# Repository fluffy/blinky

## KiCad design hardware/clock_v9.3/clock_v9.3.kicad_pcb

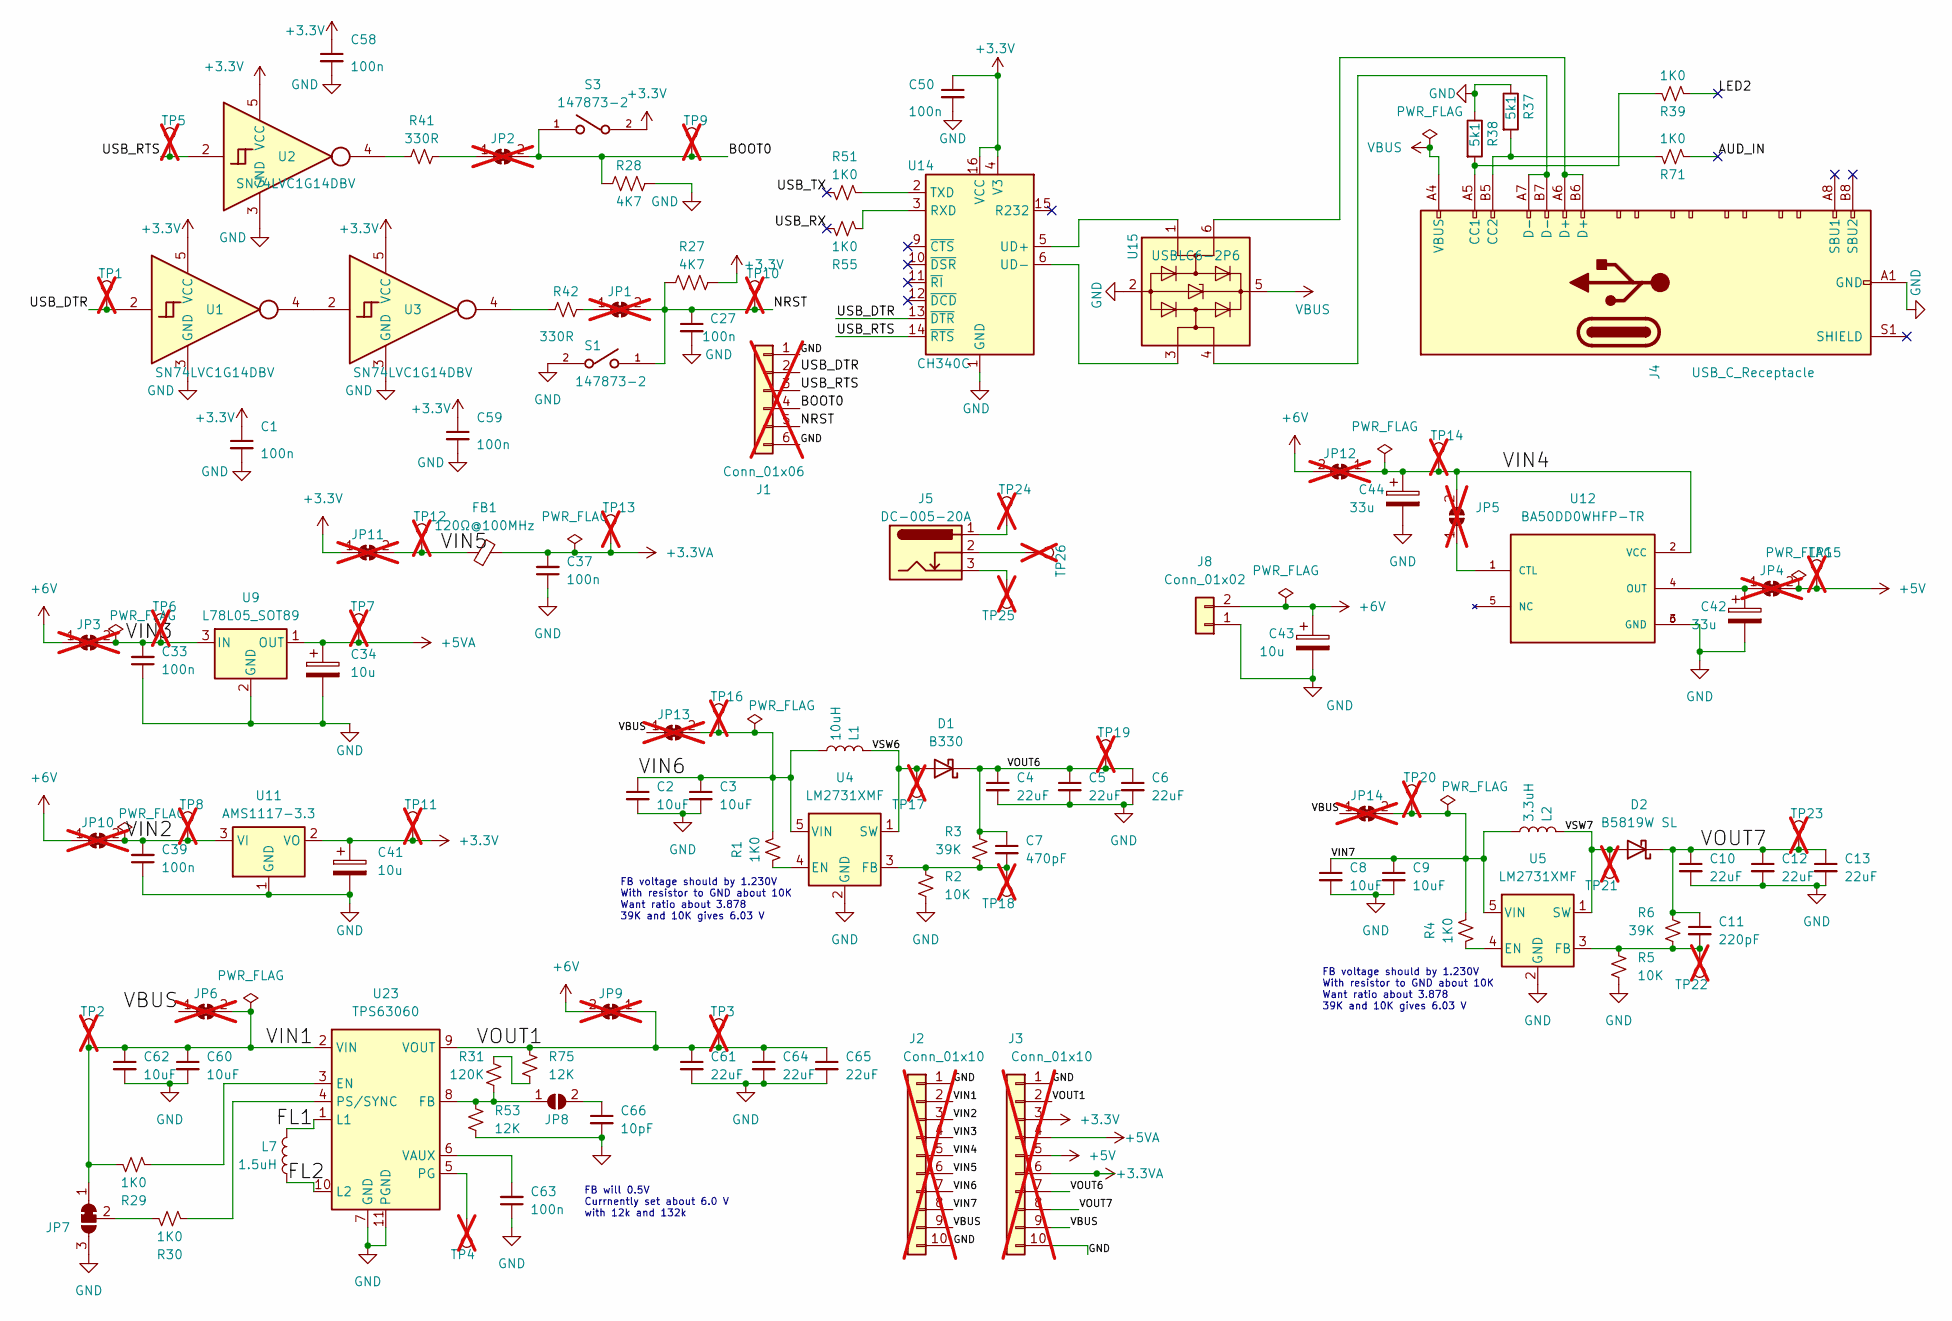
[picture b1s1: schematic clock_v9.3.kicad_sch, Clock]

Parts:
C1, C33, C39, C50, C58, C59: 100n; C_0402_1005Metric; JLCPCB Part # C307331
C2, C3, C8, C9, C60, C62: 10uF; C_0603_1608Metric; JLCPCB Part # C96446
C4, C5, C6, C10, C12, C13, C61, C64, C65: 22uF; C_0805_2012Metric; JLCPCB Part # C45783
C7: 470pF; C_0603_1608Metric; JLCPCB Part # C1620
C11: 220pF; C_0603_1608Metric; JLCPCB Part # C1603
C27, C37, C63: 100n; C_0603_1608Metric; JLCPCB Part # C14663
C34, C41, C43: 10u; CP_EIA-3216-18_Kemet-A; JLCPCB Part # C7171
C42, C44: 33u; CP_EIA-3528-21_Kemet-B; JLCPCB Part # C128342
C66: 10pF; C_0603_1608Metric; JLCPCB Part # C1634
D1: B330; D_SMC; MPN B330-13-F; JLCPCB Part # C460778
D2: B5819W SL; D_SOD-123; MPN B5819W SL; JLCPCB Part # C8598
FB1: 120Ω@100MHz; R_0603_1608Metric; JLCPCB Part # C127301
J1: Conn_01x06; PinHeader_1x06_P2.54mm_Vertical; not fitted
J2, J3: Conn_01x10; PinHeader_1x10_P2.54mm_Vertical; not fitted
J4: USB_C_Receptacle; USB_C_Receptacle_HRO_TYPE-C-31-M-12; JLCPCB Part # C165948
J5: DC-005-20A; BarrelJack_Horizontal; JLCPCB Part # C136744
J8: Conn_01x02; JST_PH_S2B-PH-SM4-TB_1x02-1MP_P2.00mm_Horizontal; JLCPCB Part # C295747
JP1, JP2, JP3, JP4, JP6, JP9, JP10, JP11, JP12, JP13, JP14: SolderJumper_2_Bridged; SolderJumper-2_P1.3mm_Bridged2Bar_RoundedPad1.0x1.5mm; not fitted
JP5: SolderJumper_2_Open; SolderJumper-2_P1.3mm_Bridged_RoundedPad1.0x1.5mm; not fitted
JP7: SolderJumper_3_Bridged12; SolderJumper-3_P1.3mm_Bridged2Bar12_RoundedPad1.0x1.5mm
JP8: SolderJumper_2_Open; SolderJumper-2_P1.3mm_Open_RoundedPad1.0x1.5mm
L1: 10uH; L_Coilcraft_XAL4040-XXX; MPN XAL4040-103MEC; JLCPCB Part # C5144883
L2: 3.3uH; L_Coilcraft_XAL4020-XXX; MPN XFL4020-332MEC; JLCPCB Part # C19191633
L7: 1.5uH; L_Coilcraft_XAL4020-XXX; MPN XFL4020-152MEC; JLCPCB Part # C3033018
R1, R4, R29, R30, R39, R51, R55, R71: 1K0; R_0603_1608Metric; JLCPCB Part # C21190
R2, R5: 10K; R_0603_1608Metric; JLCPCB Part # C25804
R3, R6: 39K; R_0603_1608Metric; JLCPCB Part # C23153
R27, R28: 4K7; R_0603_1608Metric; JLCPCB Part # C23162
R31: 120K; R_0603_1608Metric; JLCPCB Part # C25808
R37, R38: 5k1; R_0603_1608Metric; JLCPCB Part # C23186
R41, R42: 330R; R_0603_1608Metric; JLCPCB Part # C23138
R53, R75: 12K; R_0603_1608Metric; JLCPCB Part # C22790
S1, S3: 147873-2; SW_147873-2; JLCPCB Part # C266189
TP1, TP2, TP3, TP4, TP5, TP6, TP7, TP8, TP9, TP10, TP11, TP12, TP13, TP14, TP15, TP16, TP17, TP18, TP19, TP20, TP21, TP22, TP23, TP24, TP25, TP26: TestPoint_THTPad_D1.5mm_Drill0.7mm; not fitted
U1, U2, U3: SN74LVC1G14DBV; SOT-23-5; JLCPCB Rotation Offset 180
U4, U5: LM2731XMF; SOT-23-5; MPN LM2731XMFX/NOPB; JLCPCB Part # C485804
U9: L78L05_SOT89; SOT-89-3; JLCPCB Rotation Offset 180
U11: AMS1117-3.3; SOT-223-3_TabPin2; JLCPCB Rotation Offset 180
U12: BA50DD0WHFP-TR; DPAK172P1054X200-6N; PARTREV 003; JLCPCB Position Offset -1.5,0
U14: CH340C; SOIC-16_3.9x9.9mm_P1.27mm; JLCPCB Part # C84681
U15: USBLC6-2P6; SOT-666; JLCPCB Part # C2827693
U23: TPS63060; Texas_S-PWSON-N10_ThermalVias; JLCPCB Part # C48567

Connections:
+3.3V: C1.1, C41.1, C50.1, C58.1, C59.1, J3.3, JP11.1 (A), R27.1, S3.2, TP11.1, U1.5 (VCC), U2.5 (VCC), U3.5 (VCC), U11.2 (VO), U14.4 (V3), U14.16 (VCC)
+3.3VA: C37.2, FB1.2, J3.6, TP13.1
+5V: J3.5, JP4.2 (B), TP15.1
+5VA: C34.1, J3.4, TP7.1, U9.1 (OUT)
+6V: C43.1, J8.2, JP3.1 (A), JP9.2 (B), JP10.1 (A), JP12.2 (B)
/AUD_IN: R71.2
/BOOT0: J1.4, JP2.2 (B), R28.1, S3.1, TP9.1
/FL1: L7.1, U23.1 (L1)
/FL2: L7.2, U23.10 (L2)
/LED2: R39.2
/NRST: C27.1, J1.5, JP1.2 (B), R27.2, S1.1, TP10.1
/USB_DTR: J1.2, TP1.1, U1.2, U14.13 (~DTR)
/USB_RTS: J1.3, TP5.1, U2.2, U14.14 (~RTS)
/USB_RX: R55.1
/USB_TX: R51.2
/VIN1: C60.1, C62.1, J2.2, JP6.2 (B), JP7.1 (A), R29.1, TP2.1, U23.2 (VIN)
/VIN2: C39.2, J2.3, JP10.2 (B), TP8.1, U11.3 (VI)
/VIN3: C33.2, J2.4, JP3.2 (B), TP6.1, U9.3 (IN)
/VIN4: C44.1, J2.5, JP5.2 (B), JP12.1 (A), TP14.1, U12.2 (VCC)
/VIN5: FB1.1, J2.6, JP11.2 (B), TP12.1
/VIN6: C2.1, C3.1, J2.7, JP13.2 (B), L1.2, R1.1, TP16.1, U4.5 (VIN)
/VIN7: C8.1, C9.1, J2.8, JP14.2 (B), L2.2, R4.1, TP20.1, U5.5 (VIN)
/VOUT1: C61.1, C64.1, C65.1, J3.2, JP9.1 (A), R75.1, TP3.1, U23.9 (VOUT)
/VOUT6: C4.1, C5.1, C6.1, C7.1, D1.1 (K), J3.7, R3.1, TP19.1
/VOUT7: C10.1, C11.1, C12.1, C13.1, D2.1 (K), J3.8, R6.1, TP23.1
/VSW6: D1.2 (A), L1.1, TP17.1, U4.1 (SW)
/VSW7: D2.2 (A), L2.1, TP21.1, U5.1 (SW)
GND: C1.2, C2.2, C3.2, C4.2, C5.2, C6.2, C8.2, C9.2, C10.2, C12.2, C13.2, C27.2, C33.1, C34.2, C37.1, C39.1, C41.2, C42.2, C43.2, C44.2, C50.2, C58.2, C59.2, C60.2, C61.2, C62.2, C63.1, C64.2, C65.2, C66.2, J1.1, J1.6, J2.1, J2.10, J3.1, J3.10, J4.A1 (GND), J4.A12 (GND), J4.B1 (GND), J4.B12 (GND), J8.1, JP7.3 (B), R2.2, R5.2, R28.2, R37.1, R38.1, R53.2, S1.2, U1.3 (GND), U2.3 (GND), U3.3 (GND), U4.2 (GND), U5.2 (GND), U9.2 (GND), U11.1 (GND), U12.3 (GND), U12.6 (GND), U14.1 (GND), U15.2 (GND), U23.7 (GND), U23.11 (PGND)
unnamed: J4.A5 (CC1), R38.2, R39.1
unnamed: J4.B5 (CC2), R37.2, R71.1
unnamed: J4.A6 (D+), J4.B6 (D+), U15.6 (I/O1)
unnamed: J4.A7 (D-), J4.B7 (D-), U15.4 (I/O2)
unnamed: J5.1, TP24.1
unnamed: J5.2, TP26.1
unnamed: J5.3, TP25.1
unnamed: JP1.1 (A), R42.1
unnamed: JP2.1 (A), R41.2
unnamed: C42.1, JP4.1 (A), U12.4 (OUT)
unnamed: JP5.1 (A), U12.1 (CTL)
unnamed: JP7.2 (C), R30.1
unnamed: JP8.1 (A), R31.2, R53.1, U23.8 (FB)
unnamed: C66.1, JP8.2 (B)
unnamed: R31.1, R75.2
unnamed: R41.1, U2.4
unnamed: R42.2, U3.4
unnamed: U1.4, U3.2
unnamed: R1.2, U4.4 (EN)
unnamed: C7.2, R2.1, R3.2, TP18.1, U4.3 (FB)
unnamed: R4.2, U5.4 (EN)
unnamed: C11.2, R5.1, R6.2, TP22.1, U5.3 (FB)
unnamed: R55.2, U14.3 (RXD)
unnamed: R51.1, U14.2 (TXD)
unnamed: U14.5 (UD+), U15.1 (I/O1)
unnamed: U14.6 (UD-), U15.3 (I/O2)
unnamed: R29.2, U23.3 (EN)
unnamed: TP4.1, U23.5 (PG)
unnamed: R30.2, U23.4 (PS/SYNC)
unnamed: C63.2, U23.6 (VAUX)
VBUS: J2.9, J3.9, J4.A4 (VBUS), J4.A9 (VBUS), J4.B4 (VBUS), J4.B9 (VBUS), JP6.1 (A), JP13.1 (A), JP14.1 (A), U15.5 (VBUS)

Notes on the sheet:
FB voltage should by 1.230V With resistor to GND about 10K Want ratio about 3.878 39K and 10K gives 6.03 V
FB will 0.5V Currnently set about 6.0 V with 12k and 132k

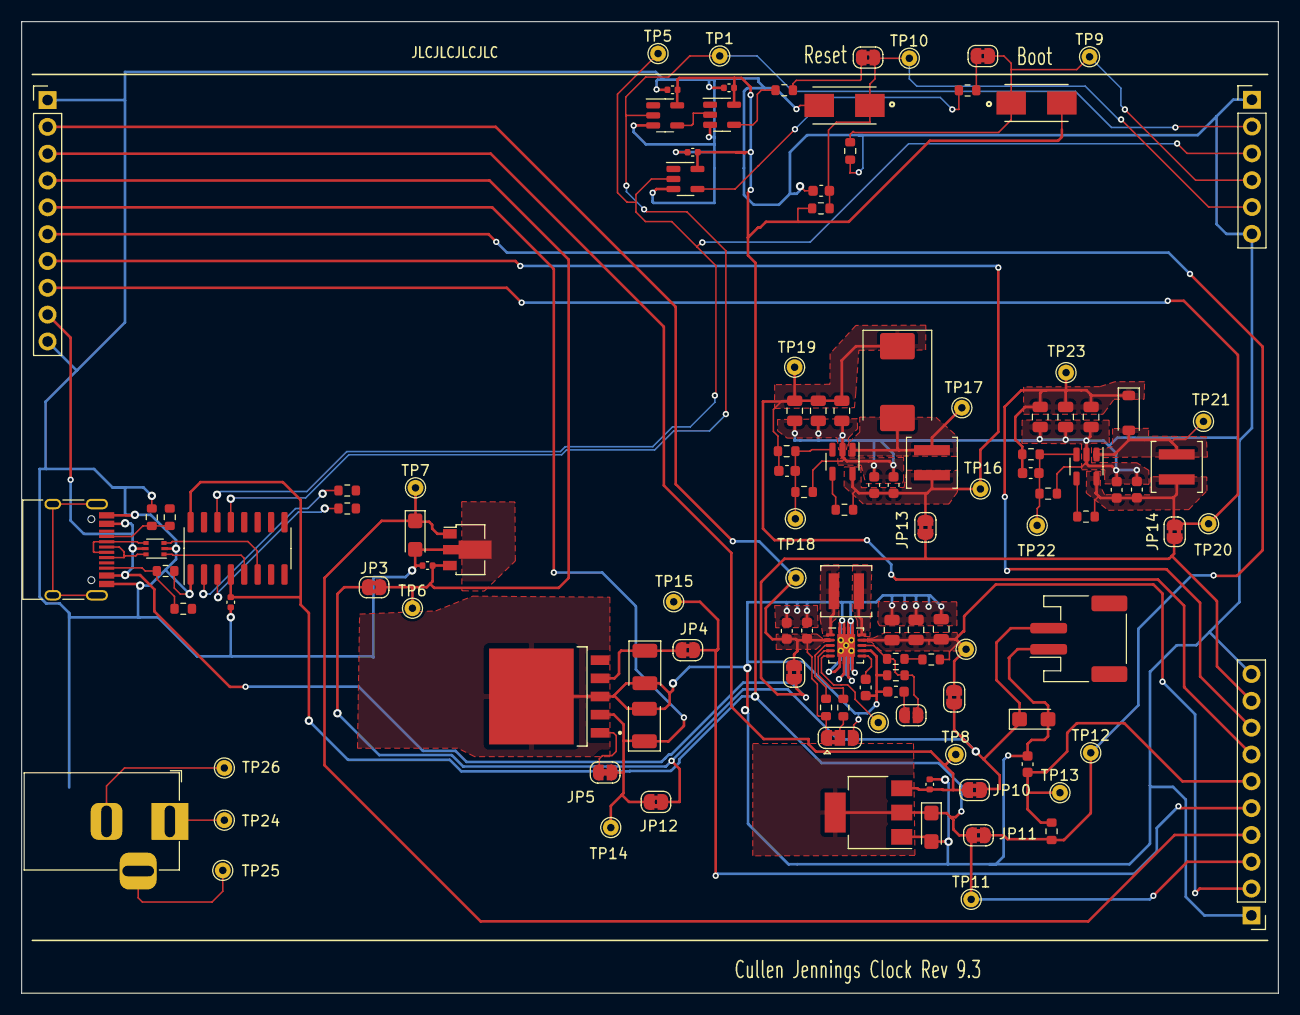
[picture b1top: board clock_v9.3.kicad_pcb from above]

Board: 2 copper layers, 119.0 x 92.0 mm, 118 parts (0 on the bottom side), 55 nets.

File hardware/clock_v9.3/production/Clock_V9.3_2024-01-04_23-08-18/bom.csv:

Designator,Footprint,Quantity,Value,LCSC Part #
"C1, C33, C39, C50, C58, C59",0402,6,100n,C307331
"C10, C12, C13, C4, C5, C6, C61, C64, C65",0805,9,22uF,C45783
C11,0603,1,220pF,C1603
"C2, C3, C60, C62, C8, C9",0603,6,10uF,C96446
"C27, C37, C63",0603,3,100n,C14663
"C34, C41, C43",CP_EIA-3216-18_Kemet-A,3,10u,C7171
"C42, C44",CP_EIA-3528-21_Kemet-B,2,33u,C128342
C66,0603,1,10pF,C1634
C7,0603,1,470pF,C1620
D1,D_SMC,1,B330,C460778
D2,D_SOD-123,1,B5819W SL,C8598
FB1,0603,1,120Ω@100MHz ,C127301
J4,USB_C_Receptacle_HRO_TYPE-C-31-M-12,1,USB_C_Receptacle,C165948
J5,BarrelJack_Horizontal,1,DC-005-20A,C136744
J8,JST_PH_S2B-PH-SM4-TB_1x02-1MP_P2.00mm_Horizontal,1,Conn_01x02,C295747
L1,L_Coilcraft_XAL4040-XXX,1,10uH,C5144883
L2,L_Coilcraft_XAL4020-XXX,1,3.3uH,C19191633
L7,L_Coilcraft_XAL4020-XXX,1,1.5uH,C3033018
"R1, R29, R30, R39, R4, R51, R55, R71",0603,8,1K0,C21190
"R2, R5",0603,2,10K,C25804
"R27, R28",0603,2,4K7,C23162
"R3, R6",0603,2,39K,C23153
R31,0603,1,120K,C25808
"R37, R38",0603,2,5k1,C23186
"R41, R42",0603,2,330R,C23138
"R53, R75",0603,2,12K,C22790
"S1, S3",SW_147873-2,2,147873-2,C266189
"U1, U2, U3",SOT-23-5,3,SN74LVC1G14DBV,C133145
U11,SOT-223-3_TabPin2,1,AMS1117-3.3,C6186
U12,DPAK172P1054X200-6N,1,BA50DD0WHFP-TR,C509718
U14,SOIC-16_3.9x9.9mm_P1.27mm,1,CH340C,C84681
U15,SOT-666,1,USBLC6-2P6,C2827693
U23,Texas_S-PWSON-N10_ThermalVias,1,TPS63060,C48567
"U4, U5",SOT-23-5,2,LM2731XMF,C485804
U9,SOT-89-3,1,L78L05_SOT89,C71136

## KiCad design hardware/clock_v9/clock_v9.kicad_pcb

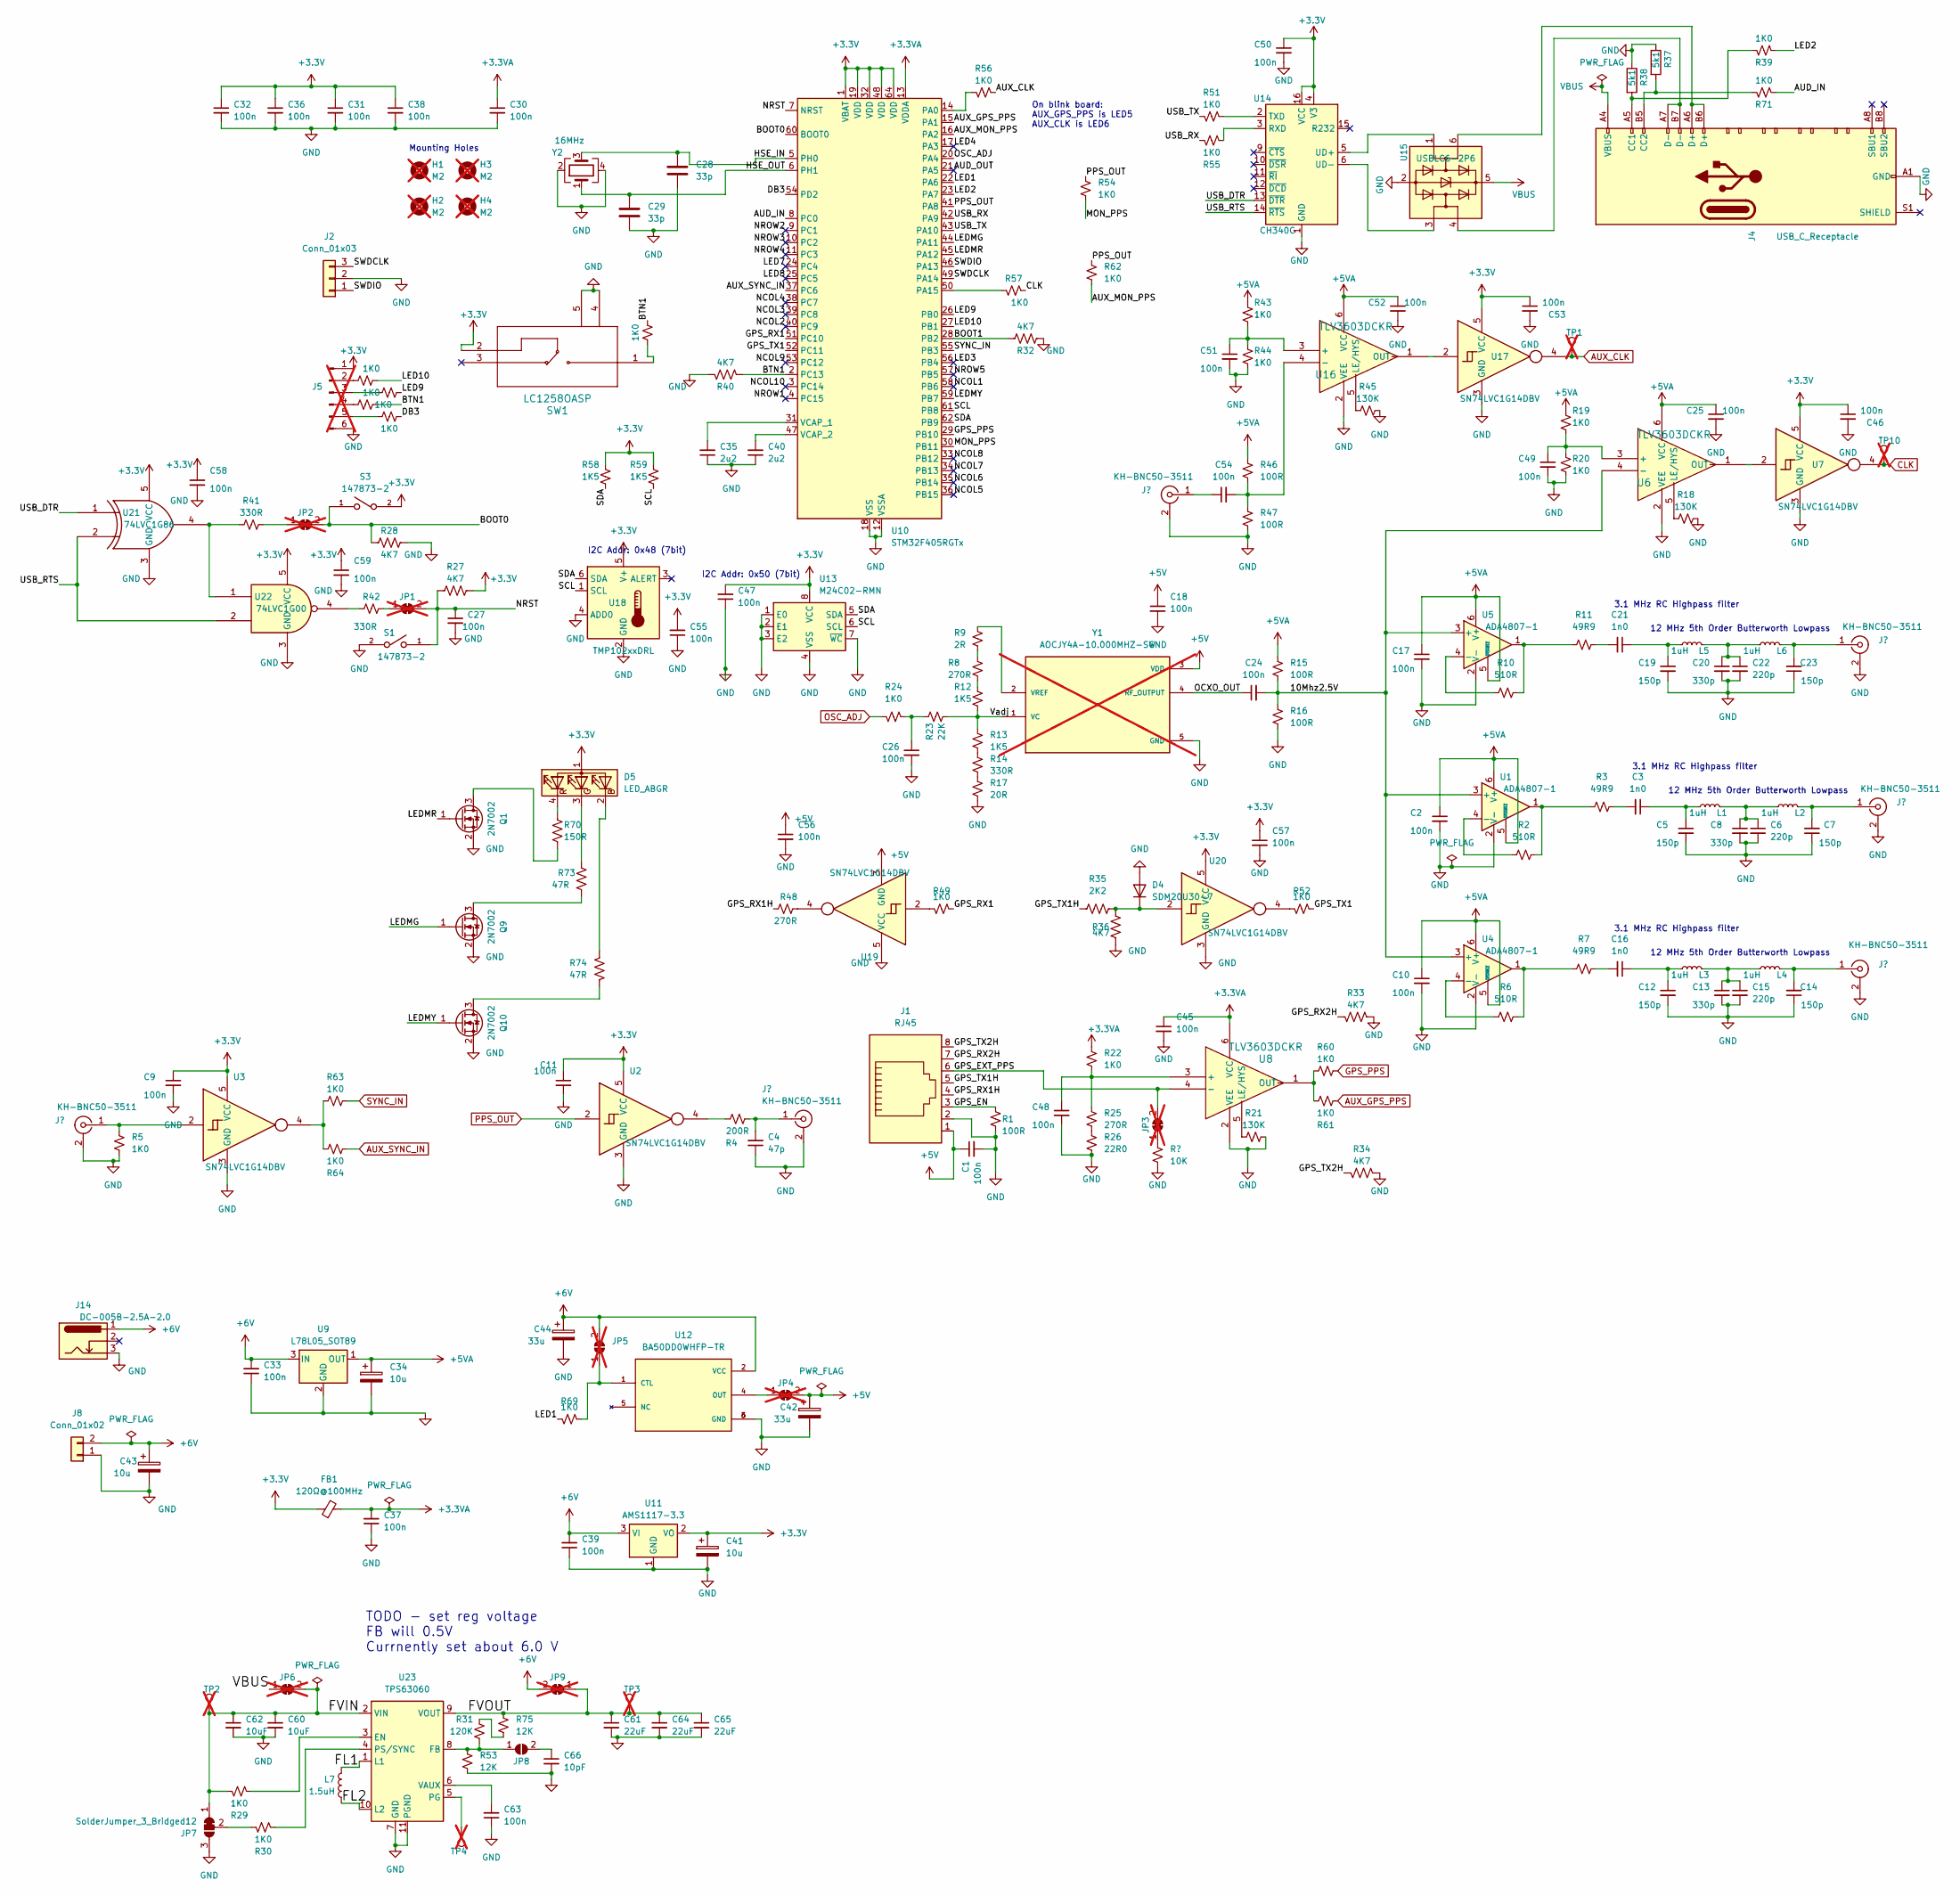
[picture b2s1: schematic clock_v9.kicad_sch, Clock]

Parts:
C1, C2, C9, C10, C11, C17, C18, C25, C26, C30, C31, C32, C33, C36, C38, C39, C45, C46, C47, C48, C49, C50, C51, C52, C53, C55, C56, C57, C58, C59: 100n; C_0402_1005Metric; JLCPCB Part # C307331
C3, C16, C21: 1n0; C_0603_1608Metric; JLCPCB Part # C1588
C4: 47p; C_0603_1608Metric; JLCPCB Part # C1671
C5, C7, C12, C14, C19, C23: 150p; C_0603_1608Metric; JLCPCB Part # C1594
C6, C15, C22: 220p; C_0603_1608Metric; JLCPCB Part # C1603
C8, C13, C20: 330p; C_0603_1608Metric; JLCPCB Part # C1664
C24, C27, C37, C54, C63: 100n; C_0603_1608Metric; JLCPCB Part # C14663
C28, C29: 33p; C_0603_1608Metric; JLCPCB Part # C1663
C34, C41, C43: 10u; CP_EIA-3216-18_Kemet-A; JLCPCB Part # C7171
C35, C40: 2u2; C_0603_1608Metric; JLCPCB Part # C23630
C42, C44: 33u; CP_EIA-3528-21_Kemet-B; JLCPCB Part # C128342
C60, C62: 10uF; C_0603_1608Metric; JLCPCB Part # C96446
C61, C64, C65: 22uF; C_0805_2012Metric; JLCPCB Part # C45783
C66: 10pF; C_0603_1608Metric; JLCPCB Part # C1634
D4: SDM20U30-7; D_SOD-523; JLCPCB Part # C91235
D5: LED_ABGR; LED_RGB_MHS110FRGBCT; MPN MHS110FRGBCT; JLCPCB Part # C496820
FB1: 120Ω@100MHz; R_0603_1608Metric; JLCPCB Part # C127301
H1, H2, H3, H4: M2; MountingHole_2.2mm_M2; not fitted
J1: RJ45; RJ45_Amphenol_RJHSE5380; JLCPCB Part # C464586
J2: Conn_01x03; JST_PH_S3B-PH-SM4-TB_1x03-1MP_P2.00mm_Horizontal; JLCPCB Part # C265101
J3, J7, J9, J10, J11, J13: KH-BNC50-3511; BNC_Amphenol_B6252HB-NPP3G-50_Horizontal-CJ; JLCPCB Part # C2837587
J4: USB_C_Receptacle; USB_C_Receptacle_HRO_TYPE-C-31-M-12; JLCPCB Part # C165948
J5: Conn_01x06_Pin; PinHeader_1x06_P2.54mm_Vertical; not fitted
J8: Conn_01x02; JST_PH_S2B-PH-SM4-TB_1x02-1MP_P2.00mm_Horizontal; JLCPCB Part # C295747
J14: DC-005B-2.5A-2.0; BarrelJack_Horizontal; JLCPCB Part # C319132
JP1, JP2, JP3, JP4, JP6, JP9: SolderJumper_2_Bridged; SolderJumper-2_P1.3mm_Bridged2Bar_RoundedPad1.0x1.5mm; not fitted
JP5: SolderJumper_2_Open; SolderJumper-2_P1.3mm_Open_RoundedPad1.0x1.5mm; not fitted
JP7: SolderJumper_3_Bridged12; SolderJumper-3_P1.3mm_Bridged2Bar12_RoundedPad1.0x1.5mm
JP8: SolderJumper_2_Open; SolderJumper-2_P1.3mm_Open_RoundedPad1.0x1.5mm
L1, L2, L3, L4, L5, L6: 1uH; L_0805_2012Metric; JLCPCB Part # C1042
L7: 1.5uH; L_Coilcraft_XAL4020-XXX; MPN XFL4020-152MEC; JLCPCB Part # C3033018
Q1, Q9, Q10: 2N7002; SOT-23; JLCPCB Rotation Offset 180
R1, R15, R16, R46, R47: 100R; R_0603_1608Metric; JLCPCB Part # C22775
R2, R6, R10: 510R; R_0603_1608Metric; JLCPCB Part # C23193
R3, R7, R11: 49R9; R_0603_1608Metric; JLCPCB Part # C23185
R4: 200R; R_0603_1608Metric; JLCPCB Part # C8218
R5, R19, R20, R22, R24, R29, R30, R39, R43, R44, R49, R51, R52, R54, R55, R56, R57, R60, R61, R62, R63, R64, R65, R66, R67, R68, R69, R71, R72: 1K0; R_0603_1608Metric; JLCPCB Part # C21190
R8, R25, R48: 270R; R_0603_1608Metric; JLCPCB Part # C22966
R9: 2R; R_0603_1608Metric; JLCPCB Part # C22977
R12, R13, R58, R59: 1K5; R_0603_1608Metric; JLCPCB Part # C22843
R14, R41, R42: 330R; R_0603_1608Metric; JLCPCB Part # C23138
R17: 20R; R_0603_1608Metric; JLCPCB Part # C22950
R18, R21, R45: 130K; R_0603_1608Metric; JLCPCB Part # C22795
R23: 22K; R_0603_1608Metric; JLCPCB Part # C31850
R26: 22R0; R_0603_1608Metric; JLCPCB Part # C23345
R27, R28, R32, R33, R34, R36, R40: 4K7; R_0603_1608Metric; JLCPCB Part # C23162
R31: 120K; R_0603_1608Metric
R35: 2K2; R_0603_1608Metric; JLCPCB Part # C4190
R37, R38: 5k1; R_0603_1608Metric; JLCPCB Part # C23186
R50: 10K; R_0603_1608Metric; JLCPCB Part # C25804
R53, R75: 12K; R_0603_1608Metric; JLCPCB Part # C22790
R70: 150R; R_0603_1608Metric; JLCPCB Part # C22808
R73, R74: 47R; R_0603_1608Metric; JLCPCB Part # C23182
S1, S3: 147873-2; SW_147873-2; JLCPCB Part # C266189
SW1: LC1258OASP; JLCPCB Part # C273412
TP1, TP2, TP3, TP4, TP10: TestPoint_THTPad_D1.5mm_Drill0.7mm; not fitted
U1, U4, U5: ADA4807-1; SOT-23-6; JLCPCB Rotation Offset 270
U2, U3, U7, U17, U19, U20: SN74LVC1G14DBV; SOT-23-5; JLCPCB Rotation Offset 180
U6, U8, U16: TLV3603DCKR; SC70_DCK_TEX; JLCPCB Part # C5213955
U9: L78L05_SOT89; SOT-89-3; JLCPCB Rotation Offset 180
U10: STM32F405RGTx; LQFP-64_10x10mm_P0.5mm; JLCPCB Rotation Offset 270
U11: AMS1117-3.3; SOT-223-3_TabPin2; JLCPCB Rotation Offset 180
U12: BA50DD0WHFP-TR; DPAK172P1054X200-6N; PARTREV 003; JLCPCB Position Offset -1.5,0
U13: M24C02-RMN; SOIC-8_3.9x4.9mm_P1.27mm; JLCPCB Rotation Offset 270
U14: CH340C; SOIC-16_3.9x9.9mm_P1.27mm; JLCPCB Part # C84681
U15: USBLC6-2P6; SOT-666; JLCPCB Part # C2827693
U18: TMP102xxDRL; SOT-563; JLCPCB Part # C99269
U21: 74LVC1G86; SOT-23-5; JLCPCB Part # C402161
U22: 74LVC1G00; SOT-23-5; JLCPCB Part # C7826
U23: TPS63060; Texas_S-PWSON-N10_ThermalVias; JLCPCB Part # C48567
Y1: AOCJY4A-10.000MHZ-SW; XTAL_AOCJY4A-10.000MHZ-SW; PARTREV 07.24.11; JLCPCB Part # C1670487; not fitted
Y2: 16MHz; Crystal_SMD_3225-4Pin_3.2x2.5mm; JLCPCB Part # C13738

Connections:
+3.3V: C9.1, C11.1, C31.1, C32.1, C36.1, C38.1, C41.1, C46.1, C47.2, C50.1, C53.1, C55.2, C57.1, C58.1, C59.1, D5.1 (A), FB1.1, J5.1, R27.1, R58.1, R59.1, S3.2, SW1.2, U2.5 (VCC), U3.5 (VCC), U7.5 (VCC), U10.1 (VBAT), U10.19 (VDD), U10.32 (VDD), U10.48 (VDD), U10.64 (VDD), U11.2 (VO), U13.8 (VCC), U14.4 (V3), U14.16 (VCC), U17.5 (VCC), U18.5 (V+), U20.5 (VCC), U21.5 (VCC), U22.5 (VCC)
+3.3VA: C30.1, C37.2, C45.1, FB1.2, R22.1, U8.6 (VCC), U10.13 (VDDA)
+5V: C1.1, C18.1, C42.1, C56.1, J1.1, JP4.2 (B), U19.3 (GND), Y1.3 (VDD)
+5VA: C2.1, C10.1, C17.1, C25.1, C34.1, C52.1, R15.1, R19.1, R43.1, R46.1, U1.5 (~DISABLE), U1.6 (V+), U4.5 (~DISABLE), U4.6 (V+), U5.5 (~DISABLE), U5.6 (V+), U6.6 (VCC), U9.1 (OUT), U16.6 (VCC)
+6V: C33.2, C39.2, C43.1, C44.1, J8.2, J14.1, JP5.2 (B), JP9.2 (B), U9.3 (IN), U11.3 (VI), U12.2 (VCC)
/10Mhz2.5V: C24.2, R15.2, R16.1, U1.3 (+), U4.3 (+), U5.3 (+), U6.4 (-)
/AUD_IN: R71.2, U10.8 (PC0)
/AUD_OUT: U10.21 (PA5)
/AUX_MON_PPS: R62.2, U10.16 (PA2)
/BOOT0: JP2.2 (B), R28.1, S3.1, U10.60 (BOOT0)
/BOOT1: R32.2, U10.28 (PB2)
/BTN1: R40.2, R66.1, R72.2, U10.2 (PC13)
/DB3: R68.1, U10.54 (PD2)
/FL1: L7.1, U23.1 (L1)
/FL2: L7.2, U23.10 (L2)
/FVIN: C60.1, C62.1, JP6.2 (B), JP7.1 (A), R29.1, TP2.1, U23.2 (VIN)
/FVOUT: C61.1, C64.1, C65.1, JP9.1 (A), R75.1, TP3.1, U23.9 (VOUT)
/GPS_EN: J1.3, R1.1
/GPS_EXT_PPS: J1.6, JP3.2 (B), U8.4 (-)
/GPS_RX1: R49.1, U10.51 (PC10)
/GPS_RX1H: J1.4, R48.2
/GPS_RX2H: J1.7, R33.2
/GPS_TX1: R52.1, U10.52 (PC11)
/GPS_TX1H: J1.5, R35.2
/GPS_TX2H: J1.8, R34.2
/HSE_IN: C28.1, U10.5 (PH0), Y2.3
/HSE_OUT: C29.1, U10.6 (PH1), Y2.1
/LED1: R69.2, U10.22 (PA6)
/LED2: R39.2, U10.23 (PA7)
/LED3: U10.56 (PB4)
/LED4: U10.17 (PA3)
/LED7: U10.24 (PC4)
/LED8: U10.25 (PC5)
/LED9: R67.1, U10.26 (PB0)
/LED10: R65.1, U10.27 (PB1)
/LEDMG: Q9.1 (G), U10.44 (PA11)
/LEDMR: Q1.1 (G), U10.45 (PA12)
/LEDMY: Q10.1 (G), U10.59 (PB7)
/MON_PPS: R54.2, U10.30 (PB11)
/NCOL1: U10.58 (PB6)
/NCOL2: U10.40 (PC9)
/NCOL3: U10.39 (PC8)
/NCOL4: U10.38 (PC7)
/NCOL5: U10.36 (PB15)
/NCOL6: U10.35 (PB14)
/NCOL7: U10.34 (PB13)
/NCOL8: U10.33 (PB12)
/NCOL9: U10.53 (PC12)
/NCOL10: U10.3 (PC14)
/NROW1: U10.4 (PC15)
/NROW2: U10.9 (PC1)
/NROW3: U10.10 (PC2)
/NROW4: U10.11 (PC3)
/NROW5: U10.57 (PB5)
/NRST: C27.1, JP1.2 (B), R27.2, S1.1, U10.7 (NRST)
/OCXO_OUT: C24.1, Y1.4 (RF_OUTPUT)
/SCL: R59.2, U10.61 (PB8), U13.6 (SCL), U18.1 (SCL)
/SDA: R58.2, U10.62 (PB9), U13.5 (SDA), U18.6 (SDA)
/SWDCLK: J2.3, U10.49 (PA14)
/SWDIO: J2.1, U10.46 (PA13)
/USB_DTR: U14.13 (~DTR), U21.1
/USB_RTS: U14.14 (~RTS), U21.2, U22.2
/USB_RX: R55.1, U10.42 (PA9)
/USB_TX: R51.2, U10.43 (PA10)
/Vadj: R12.2, R13.1, R23.2, Y1.1 (VC)
AUX_CLK: R56.1, TP1.1, U17.4
AUX_GPS_PPS: R61.2, U10.15 (PA1)
AUX_SYNC_IN: R64.1, U10.37 (PC6)
CLK: R57.1, TP10.1, U7.4
GND: C1.2, C2.2, C4.1, C5.2, C6.2, C7.1, C8.2, C9.2, C10.2, C11.2, C12.2, C13.2, C14.1, C15.2, C17.2, C18.2, C19.2, C20.2, C22.2, C23.1, C25.2, C26.2, C27.2, C28.2, C29.2, C30.2, C31.2, C32.2, C33.1, C34.2, C35.1, C36.2, C37.1, C38.2, C39.1, C40.1, C41.2, C42.2, C43.2, C44.2, C45.2, C46.2, C47.1, C48.2, C49.2, C50.2, C51.2, C52.2, C53.2, C55.1, C56.2, C57.2, C58.2, C59.2, C60.2, C61.2, C62.2, C63.1, C64.2, C65.2, C66.2, D4.2 (A), J1.2, J2.2, J3.2 (Ext), J4.A1 (GND), J4.A12 (GND), J4.B1 (GND), J4.B12 (GND), J5.6, J7.2 (Ext), J8.1, J9.2 (Ext), J10.2 (Ext), J11.2 (Ext), J13.2 (Ext), J14.3, JP7.3 (B), Q1.2 (S), Q9.2 (S), Q10.2 (S), R1.2, R5.2, R16.2, R17.2, R18.2, R20.2, R21.2, R26.2, R28.2, R32.1, R33.1, R34.1, R36.1, R37.1, R38.1, R40.1, R44.2, R45.2, R47.2, R50.2, R53.2, S1.2, SW1.4, SW1.5, U1.2 (V-), U2.3 (GND), U3.3 (GND), U4.2 (V-), U5.2 (V-), U6.2 (VEE), U7.3 (GND), U8.2 (VEE), U9.2 (GND), U10.12 (VSSA), U10.18 (VSS), U10.63 (VSS), U11.1 (GND), U12.3 (GND), U12.6 (GND), U13.1 (E0), U13.2 (E1), U13.3 (E2), U13.4 (VSS), U13.7 (~WC), U14.1 (GND), U15.2 (GND), U16.2 (VEE), U17.3 (GND), U18.2 (GND), U18.4 (ADD0), U19.5 (VCC), U20.3 (GND), U21.3 (GND), U22.3 (GND), U23.7 (GND), U23.11 (PGND), Y1.5 (GND), Y2.2, Y2.4
GPS_PPS: R60.1, U10.29 (PB10)
unnamed: C3.1, C5.1, L1.1
unnamed: C3.2, R3.2
unnamed: C6.1, C8.1, L1.2, L2.2
unnamed: C12.1, C16.1, L3.1
unnamed: C13.1, C15.1, L3.2, L4.2
unnamed: C16.2, R7.2
unnamed: C19.1, C21.1, L5.1
unnamed: C20.1, C22.1, L5.2, L6.2
unnamed: C21.2, R11.2
unnamed: C26.1, R23.1, R24.1
unnamed: D4.1 (K), R35.1, R36.2, U20.2
unnamed: D5.2 (BK), R74.1
unnamed: D5.3 (GK), R73.2
unnamed: D5.4 (RK), R70.2
unnamed: C23.2, J3.1 (In), L6.1
unnamed: J4.A5 (CC1), R38.2, R39.1
unnamed: J4.B5 (CC2), R37.2, R71.1
unnamed: J4.A6 (D+), J4.B6 (D+), U15.6 (I/O1)
unnamed: J4.A7 (D-), J4.B7 (D-), U15.4 (I/O2)
unnamed: J5.2, R65.2
unnamed: J5.3, R67.2
unnamed: J5.4, R66.2
unnamed: J5.5, R68.2
unnamed: C54.1, J7.1 (In)
unnamed: J9.1 (In), R5.1, U3.2
unnamed: C4.2, J10.1 (In), R4.2
unnamed: C14.2, J11.1 (In), L4.1
unnamed: C7.2, J13.1 (In), L2.1
unnamed: JP1.1 (A), R42.1
unnamed: JP2.1 (A), R41.2
unnamed: JP3.1 (A), R50.1
unnamed: JP4.1 (A), U12.4 (OUT)
unnamed: JP5.1 (A), R69.1, U12.1 (CTL)
unnamed: JP7.2 (C), R30.1
unnamed: JP8.1 (A), R31.2, R53.1, U23.8 (FB)
unnamed: C66.1, JP8.2 (B)
unnamed: Q1.3 (D), R70.1
unnamed: Q9.3 (D), R73.1
unnamed: Q10.3 (D), R74.2
unnamed: R2.2, R3.1, U1.1
unnamed: R4.1, U2.4
unnamed: R6.2, R7.1, U4.1
unnamed: R8.1, R9.2
unnamed: R10.2, R11.1, U5.1
unnamed: R8.2, R12.1
unnamed: R13.2, R14.1
unnamed: R14.2, R17.1
unnamed: R25.2, R26.1
unnamed: R31.1, R75.2
unnamed: R41.1, U21.4, U22.1
unnamed: R42.2, U22.4
unnamed: R48.1, U19.4
unnamed: R49.2, U19.2
unnamed: R52.2, U20.4
unnamed: R63.2, R64.2, U3.4
unnamed: R72.1, SW1.1
unnamed: R2.1, U1.4 (-)
unnamed: R6.1, U4.4 (-)
unnamed: R10.1, U5.4 (-)
unnamed: C49.1, R19.2, R20.1, U6.3 (+)
unnamed: R18.1, U6.5 (LE/HYS)
unnamed: U6.1 (OUT), U7.2
unnamed: C48.1, R22.2, R25.1, U8.3 (+)
unnamed: R21.1, U8.5 (LE/HYS)
unnamed: R60.2, R61.1, U8.1 (OUT)
unnamed: R56.2, U10.14 (PA0)
unnamed: R57.2, U10.50 (PA15)
unnamed: C35.2, U10.31 (VCAP_1)
unnamed: C40.2, U10.47 (VCAP_2)
unnamed: R55.2, U14.3 (RXD)
unnamed: R51.1, U14.2 (TXD)
unnamed: U14.5 (UD+), U15.1 (I/O1)
unnamed: U14.6 (UD-), U15.3 (I/O2)
unnamed: C51.1, R43.2, R44.1, U16.3 (+)
unnamed: C54.2, R46.2, R47.1, U16.4 (-)
unnamed: R45.1, U16.5 (LE/HYS)
unnamed: U16.1 (OUT), U17.2
unnamed: R29.2, U23.3 (EN)
unnamed: TP4.1, U23.5 (PG)
unnamed: R30.2, U23.4 (PS/SYNC)
unnamed: C63.2, U23.6 (VAUX)
unnamed: R9.1, Y1.2 (VREF)
OSC_ADJ: R24.2, U10.20 (PA4)
PPS_OUT: R54.1, R62.1, U2.2, U10.41 (PA8)
SYNC_IN: R63.1, U10.55 (PB3)
VBUS: J4.A4 (VBUS), J4.A9 (VBUS), J4.B4 (VBUS), J4.B9 (VBUS), JP6.1 (A), U15.5 (VBUS)

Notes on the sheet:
On blink board: AUX_GPS_PPS is LED5 AUX_CLK is LED6
Mounting Holes
3.1 MHz RC Highpass filter
12 MHz 5th Order Butterworth Lowpass
TODO - set reg voltage FB will 0.5V Currnently set about 6.0 V
I2C Addr: 0x48 (7bit)
I2C Addr: 0x50 (7bit)

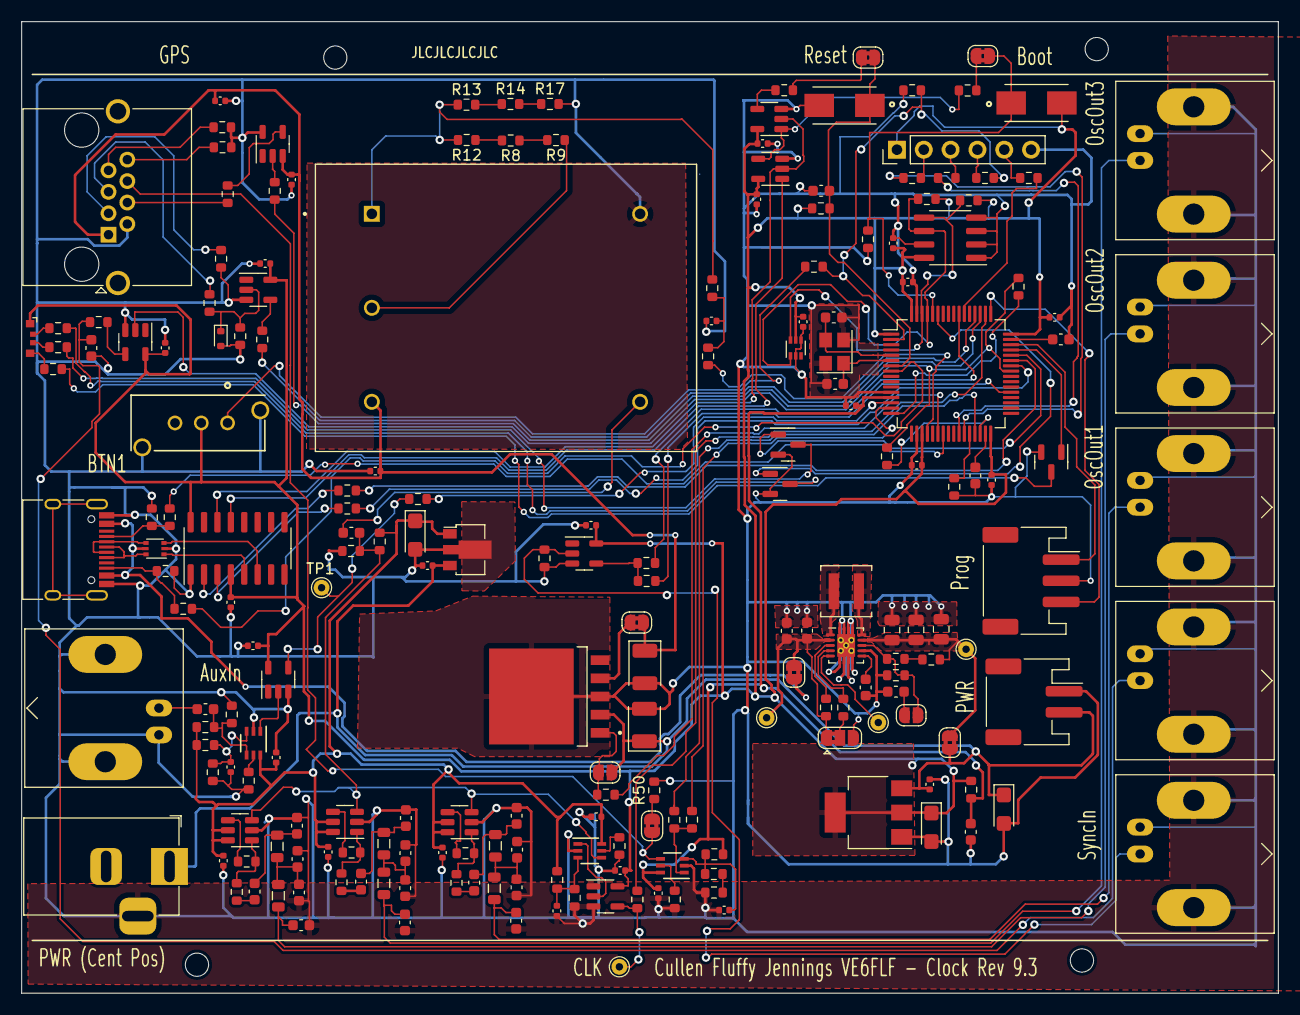
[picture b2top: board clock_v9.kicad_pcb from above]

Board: 2 copper layers, 119.0 x 92.0 mm, 212 parts (0 on the bottom side), 137 nets.

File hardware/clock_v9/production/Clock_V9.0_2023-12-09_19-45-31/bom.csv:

Designator,Footprint,Quantity,Value,LCSC Part #
"C1, C10, C11, C17, C18, C2, C25, C26, C30, C31, C32, C33, C36, C38, C39, C45, C46, C47, C48, C49, C50, C51, C52, C53, C55, C9",0402,26,100n,C307331
"C12, C14, C19, C23, C5, C7",0603,6,150p,C1594
"C13, C20, C8",0603,3,330p,C1664
"C15, C22, C6",0603,3,220p,C1603
"C16, C21, C3",0603,3,1n0,C1588
"C24, C27, C37, C54",0603,4,100n,C14663
"C28, C29",0603,2,33p,C1663
"C34, C41, C43",CP_EIA-3216-18_Kemet-A,3,10u,C7171
"C35, C40",0603,2,2u2,C23630
C4,0603,1,47p,C1671
"C42, C44",CP_EIA-3528-21_Kemet-B,2,33u,C128342
D1,0603,1,LED-R,C94869
D2,0603,1,LED-G,C125093
D3,0603,1,LED-Y,C72038
D4,D_SOD-123,1,1N4148W,C191023
D5,LED_RGB_MHS110FRGBCT,1,LED_ABGR,C496820
FB1,0603,1,120Ω@100MHz ,C127301
J1,RJ45_Amphenol_RJHSE5380,1,RJ45,C464586
"J10, J11, J13, J3, J7, J9",BNC_Amphenol_B6252HB-NPP3G-50_Horizontal-CJ,6,KH-BNC50-3511,C2837587
J14,BarrelJack_Horizontal,1,DC-005I-5A-2.5,C2689704
J2,JST_PH_S3B-PH-SM4-TB_1x03-1MP_P2.00mm_Horizontal,1,Conn_01x03,C265101
J4,USB_C_Receptacle_HRO_TYPE-C-31-M-12,1,USB_C_Receptacle,C165948
J8,JST_PH_S2B-PH-SM4-TB_1x02-1MP_P2.00mm_Horizontal,1,Conn_01x02,C295747
"L1, L2, L3, L4, L5, L6",0805,6,1uH,C1042
"Q1, Q10, Q9",SOT-23,3,2N7002,C8545
Q2,SOT-23,1,S8550,C105432
"Q3, Q4, Q5",SOT-23,3,S8050,C2150
"R1, R15, R16, R29, R30, R31, R46, R47",0603,8,100R,C22775
"R10, R2, R6",0603,3,510R,C23193
"R11, R3, R7",0603,3,49R9,C23185
"R12, R13, R58, R59",0603,4,1K5,C22843
R14,0603,1,330R,C23138
R17,0603,1,20R,C22950
"R18, R21, R45",0603,3,130K,C22795
"R19, R20, R22, R24, R39, R41, R42, R43, R44, R49, R5, R51, R52, R53, R54, R55, R56, R57, R60, R61, R62, R63, R64, R65, R66, R67, R68, R69, R71, R72",0603,30,1K0,C21190
R23,0603,1,22K,C31850
"R25, R8",0603,2,270R,C22966
R26,0603,1,22R0,C23345
"R27, R28, R32, R33, R34, R36, R40, R48",0603,8,4K7,C23162
R35,0603,1,2K2,C4190
"R37, R38",0603,2,5k1,C23186
R4,0603,1,200R,C8218
R50,0603,1,10K,C25804
R70,0603,1,150R,C22808
"R73, R74",0603,2,47R,C23182
R9,0603,1,2R,C22977
"S1, S3",SW_147873-2,2,147873-2,C266189
SW1,LC1258OASP,1,LC1258OASP,C273412
"U1, U4, U5",SOT-23-6,3,ADA4807-1,C2058411
U10,LQFP-64_10x10mm_P0.5mm,1,STM32F405RGTx,C15742
U11,SOT-223-3_TabPin2,1,AMS1117-3.3,C6186
U12,DPAK172P1054X200-6N,1,BA50DD0WHFP-TR,C509718
U13,SOIC-8_3.9x4.9mm_P1.27mm,1,M24C02-RMN,C83836
U14,SOIC-16_3.9x9.9mm_P1.27mm,1,CH340C,C84681
U15,SOT-666,1,USBLC6-2P6,C2827693
"U16, U6, U8",SC70_DCK_TEX,3,TLV3603DCKR,C5213955
"U17, U2, U3, U7",SOT-23-5,4,SN74LVC1G14DBV,C133145
U18,SOT-563,1,TMP102xxDRL,C99269
U9,SOT-89-3,1,L78L05_SOT89,C71136
Y2,Crystal_SMD_3225-4Pin_3.2x2.5mm,1,16MHz ,C13738
